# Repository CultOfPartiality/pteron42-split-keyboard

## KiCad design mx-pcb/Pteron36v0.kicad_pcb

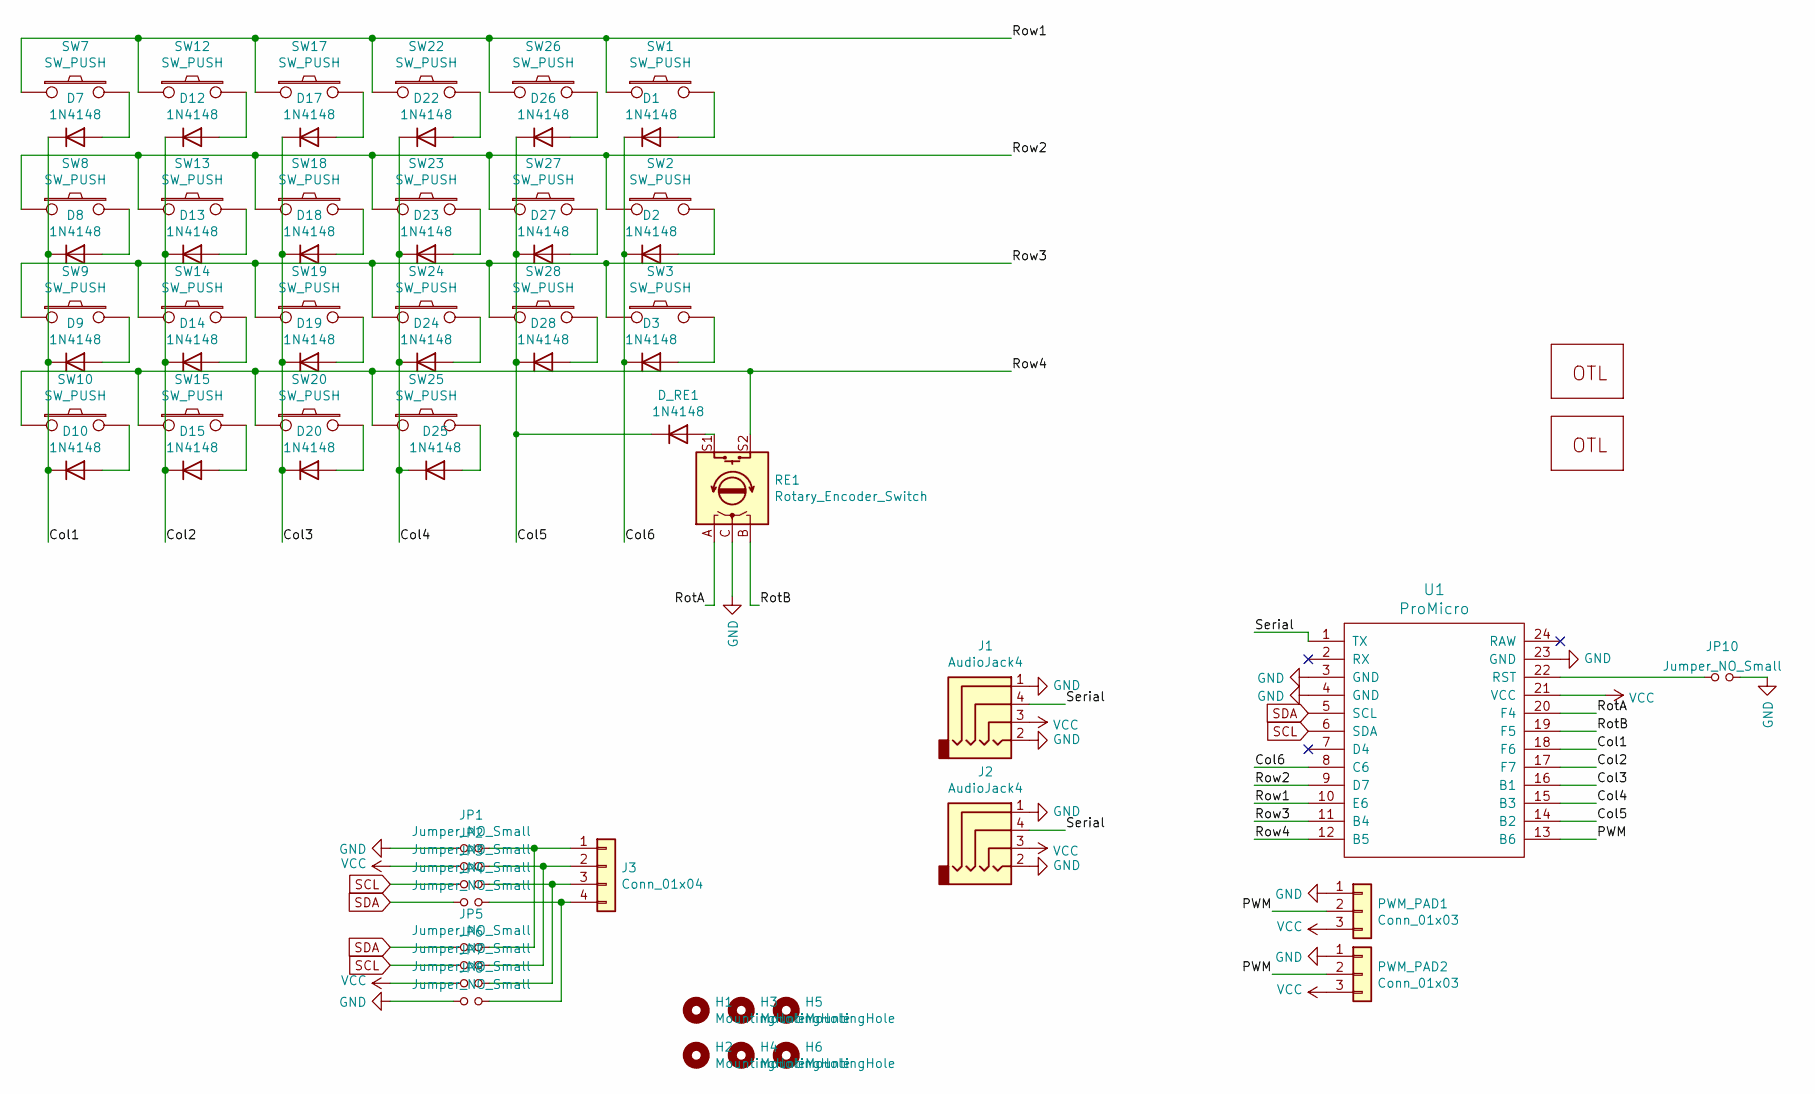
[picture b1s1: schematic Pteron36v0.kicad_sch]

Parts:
D1, D2, D3, D7, D8, D9, D10, D12, D13, D14, D15, D17, D18, D19, D20, D22, D23, D24, D25, D26, D27, D28: 1N4148; Diode-dual
D_RE1: 1N4148; Diode-dual
H1, H2, H3, H4, H5, H6: MountingHole; MountingHole_2.2mm_M2_Pad
J1, J2: AudioJack4; TRRS-PJ-320A
J3: Conn_01x04; OLED_4Pin_outline
JP1, JP2, JP3, JP4, JP5, JP6, JP7, JP8: Jumper_NO_Small; PAD-JUMPER-2-NO_NO_SILK
JP10: Jumper_NO_Small; SolderJumper-flip-2_P1.3mm_Open_Pad1.0x1.5mm
LOGO3, LOGO4: LOGO-OTL; peacock-medium
PWM_PAD1, PWM_PAD2: Conn_01x03; 1X03_LONGPADS
RE1: Rotary_Encoder_Switch; RotaryEncoder_Alps_EC11E-Switch_Vertical_H20mm
SW1, SW2, SW3, SW7, SW8, SW9, SW10, SW12, SW13, SW14, SW15, SW17, SW18, SW19, SW20, SW22, SW23, SW24, SW25, SW26, SW27, SW28: SW_PUSH; Hybrid_PCB_100H_Dual_hole
U1: ProMicro

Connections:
/Col1: D7.1 (K), D8.1 (K), D9.1 (K), D10.1 (K), U1.18 (F6)
/Col2: D12.1 (K), D13.1 (K), D14.1 (K), D15.1 (K), U1.17 (F7)
/Col3: D17.1 (K), D18.1 (K), D19.1 (K), D20.1 (K), U1.16 (B1)
/Col4: D22.1 (K), D23.1 (K), D24.1 (K), D25.1 (K), U1.15 (B3)
/Col5: D26.1 (K), D27.1 (K), D28.1 (K), D_RE1.1 (K), U1.14 (B2)
/Col6: D1.1 (K), D2.1 (K), D3.1 (K), U1.8 (C6)
/PWM: PWM_PAD1.2, PWM_PAD2.2, U1.13 (B6)
/RotA: RE1.A, U1.20 (F4)
/RotB: RE1.B, U1.19 (F5)
/Row1: SW1.1, SW7.1, SW12.1, SW17.1, SW22.1, SW26.1, U1.10 (E6)
/Row2: SW2.1, SW8.1, SW13.1, SW18.1, SW23.1, SW27.1, U1.9 (D7)
/Row3: SW3.1, SW9.1, SW14.1, SW19.1, SW24.1, SW28.1, U1.11 (B4)
/Row4: RE1.S2, SW10.1, SW15.1, SW20.1, SW25.1, U1.12 (B5)
/Serial: J1.4, J2.4, U1.1 (TX)
GND: J1.1, J1.2, J2.1, J2.2, JP1.1, JP8.1, JP10.2, PWM_PAD1.1, PWM_PAD2.1, RE1.C, U1.3 (GND), U1.4 (GND), U1.23 (GND)
unnamed: D1.2 (A), SW1.2
unnamed: D2.2 (A), SW2.2
unnamed: D3.2 (A), SW3.2
unnamed: D7.2 (A), SW7.2
unnamed: D8.2 (A), SW8.2
unnamed: D9.2 (A), SW9.2
unnamed: D10.2 (A), SW10.2
unnamed: D12.2 (A), SW12.2
unnamed: D13.2 (A), SW13.2
unnamed: D14.2 (A), SW14.2
unnamed: D15.2 (A), SW15.2
unnamed: D17.2 (A), SW17.2
unnamed: D18.2 (A), SW18.2
unnamed: D19.2 (A), SW19.2
unnamed: D20.2 (A), SW20.2
unnamed: D22.2 (A), SW22.2
unnamed: D23.2 (A), SW23.2
unnamed: D24.2 (A), SW24.2
unnamed: D25.2 (A), SW25.2
unnamed: D26.2 (A), SW26.2
unnamed: D27.2 (A), SW27.2
unnamed: D28.2 (A), SW28.2
unnamed: D_RE1.2 (A), RE1.S1
unnamed: J3.1, JP1.2, JP5.2
unnamed: J3.2, JP2.2, JP6.2
unnamed: J3.3, JP3.2, JP7.2
unnamed: J3.4, JP4.2, JP8.2
unnamed: JP10.1, U1.22 (RST)
SCL: JP3.1, JP6.1, U1.6 (SDA)
SDA: JP4.1, JP5.1, U1.5 (SCL)
VCC: J1.3, J2.3, JP2.1, JP7.1, PWM_PAD1.3, PWM_PAD2.3, U1.21 (VCC)

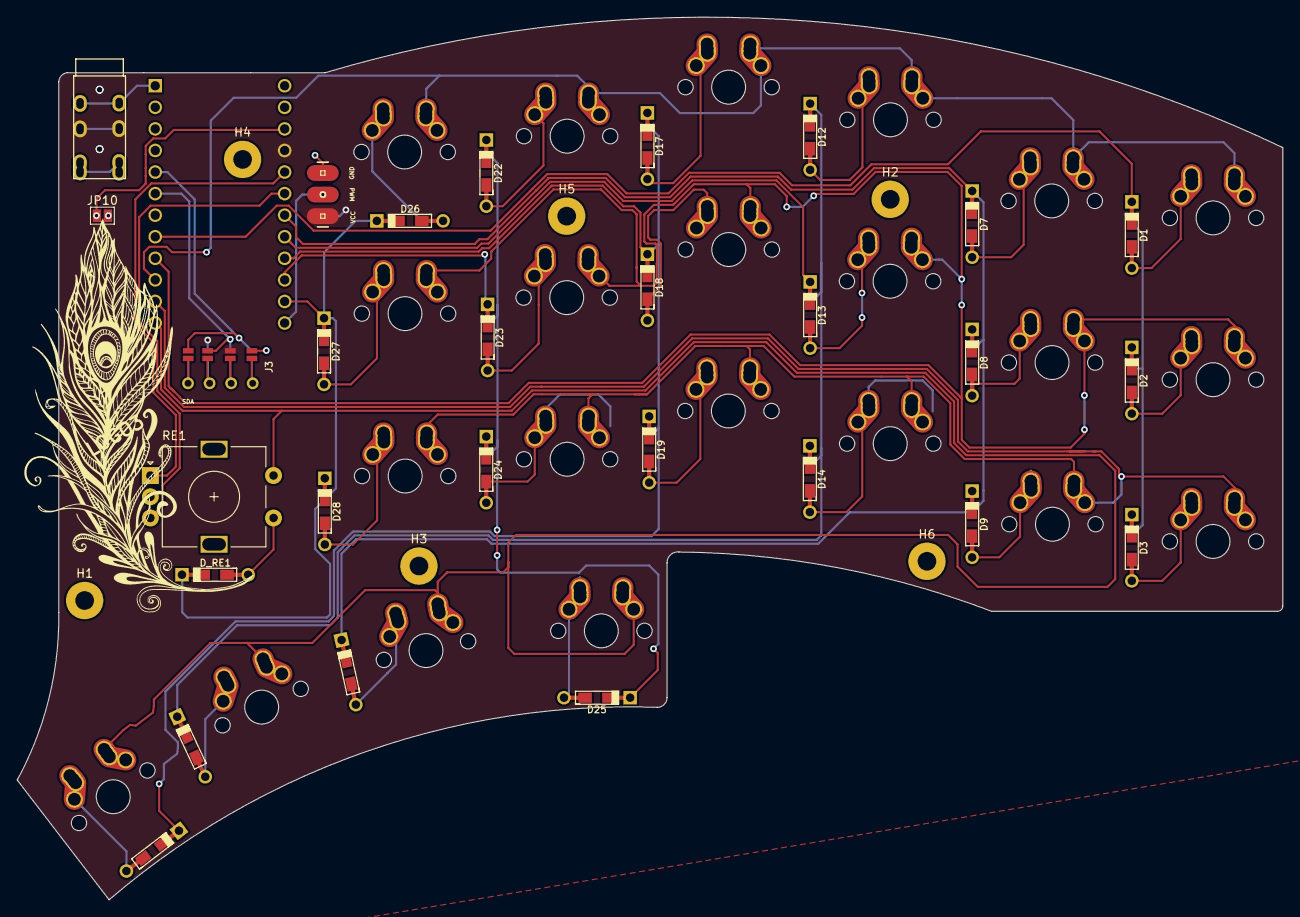
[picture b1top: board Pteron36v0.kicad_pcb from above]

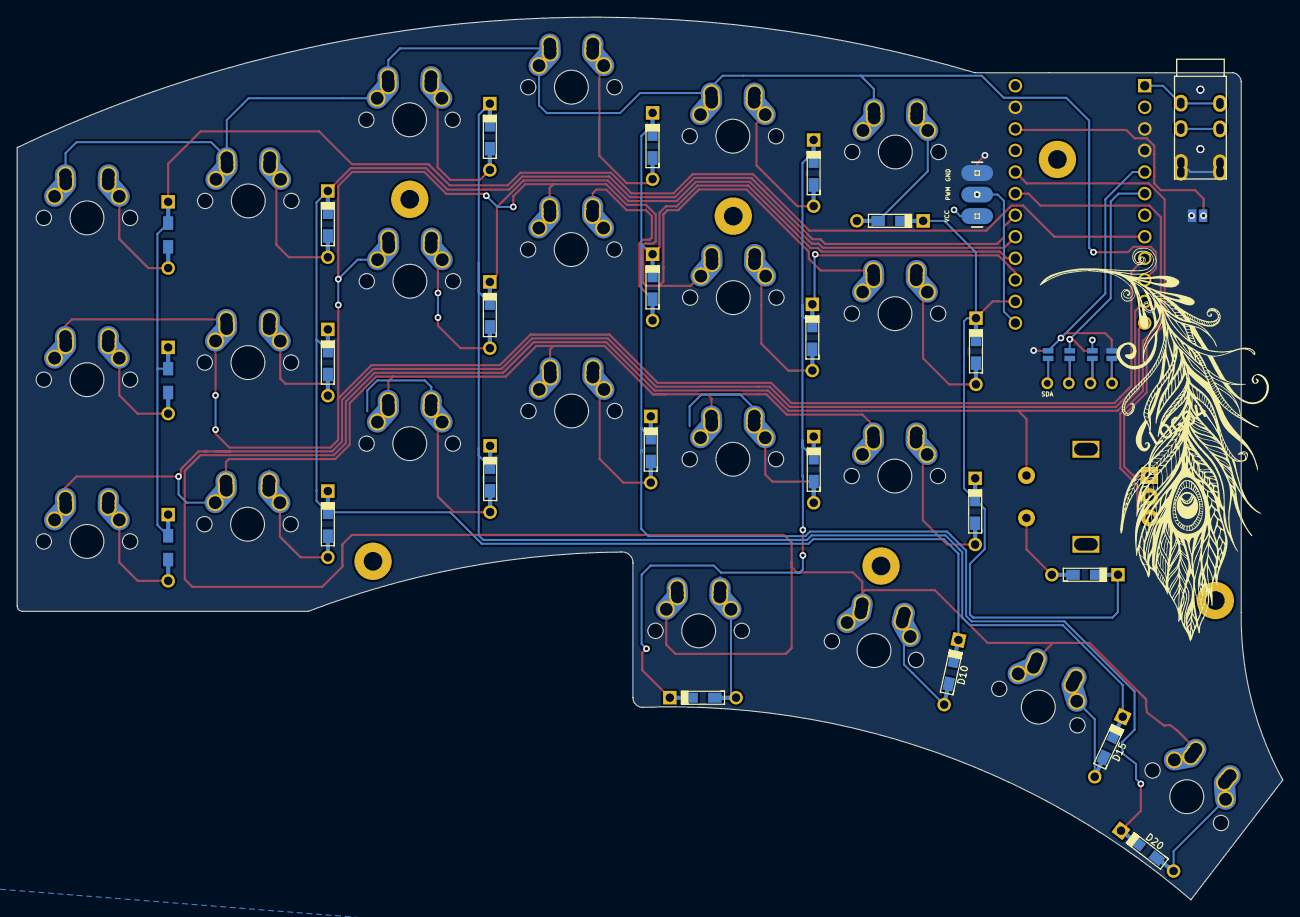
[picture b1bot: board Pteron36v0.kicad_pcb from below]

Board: 2 copper layers, 149.0 x 103.9 mm, 69 parts (10 on the bottom side), 46 nets.

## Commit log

2024-02-22 First pass at 42 keys
    Sent off to be made
